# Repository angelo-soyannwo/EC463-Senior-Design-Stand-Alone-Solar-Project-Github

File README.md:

# Sol: An Alternative Off-grid Solar Configuration

## Quick-Start Info

### Structural Hardware

The hardware of our system consists of a frame with solar panels on either side, and a pair of reflectors in between. These reflectors slide diagonally up and down, and sideways along the rails of the frame, moved a stepper motor on either side and ball screws as the linear actuator. 3D printed components are used for interface between different parts, such as the stepper motor mount, sliding face plates, and ball screw rod attachers. Housing has also been developed for our PCBs, battery, and solar charge controller.

### Electronic Hardware

Most of our electronic pieces fit on a PCB. The light sensors and limit switches fit on the solar panels and rails of the frame respectively. The components on the PCB are: 2 Rpi Pico W's, a motor driver, buttons for Pico reset and manual motor control, 2 current sensors, and a temperature sensor. A Renogy solar charge controller is used externally to charge our battery with the solar panel, as well as power our system along with any other load.

### Control Pico Software

Our control software controls the movement of our reflectors through the stepper motors. The two stepper motors are connected in parallel to just one motor driver, so the code is made simple. Upon startup, the program moves the reflectors to their bottom-most position, where it will hit the bottom limit switch and begins tracking its position through step count. As of now, the position tracking is not an integral part of the system, since the program allows the reflectors to move upwards or downwards until they hit the limit switches; the position can be used for other purposes in the future. After startup and every ten seconds, the reflectors will check the light sensor readings, move a certain number of steps in a direction determined from the previous iteration, and check the light reading again. Based on the difference between the two readings, it will continue to move in the direction with more light or stop moving when the difference no longer passes a certain threshold. All of these parameters can be set in the software, including time between iterations and light difference threshold. Additionally, data from the light sensors are sent to our database on each iteration.

### Monitoring Pico Software

The monitoring software keeps track of charge and discharge current and voltage, and temperature of our system within the housing. It does so using two current/voltage sensor and one temperature sensor. The program first connects to WiFi, then begins the normal operation during which it sends data to our database every few seconds.

### Web Application

The web application uses a MERN stack (MongoDB, Express.js, React, Node.js). The web app takes data from our database on MongoDB, which in turn has data uploaded from our Pico servers. The user interface of the web app allows users to create an account, create arrays of our solar modules, and monitor solar panel output power, solar irradiation, and temperature across time. If any anomaly is detected, the user will receive an email such that they can check up on the system as soon as they can.

Link to Web Application: https://sol-ec-464-team-15.netlify.app/

Solar Array Id: 65539e775435e37264e3e6ff

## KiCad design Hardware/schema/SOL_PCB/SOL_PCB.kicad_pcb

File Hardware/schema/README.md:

# Brief PCB Netlist Explanation

Netlist Explanations :
 - Load + = Load from solar charge controller
 - Load - = Return path from solar charge controller. This is ground.
 - Vin P + = Positive from solar panels
 - Vin P - = Negative from solar panels
 - 3.3V_M = 3.3V from monitoring pico
 - 3.3V_C = 3.3V from control pico
 - 5V = Input from a 12V-5V converter. This is an external component
 - VCC = Vin -  from the INA219. This is 12V, and is idential to Load+.

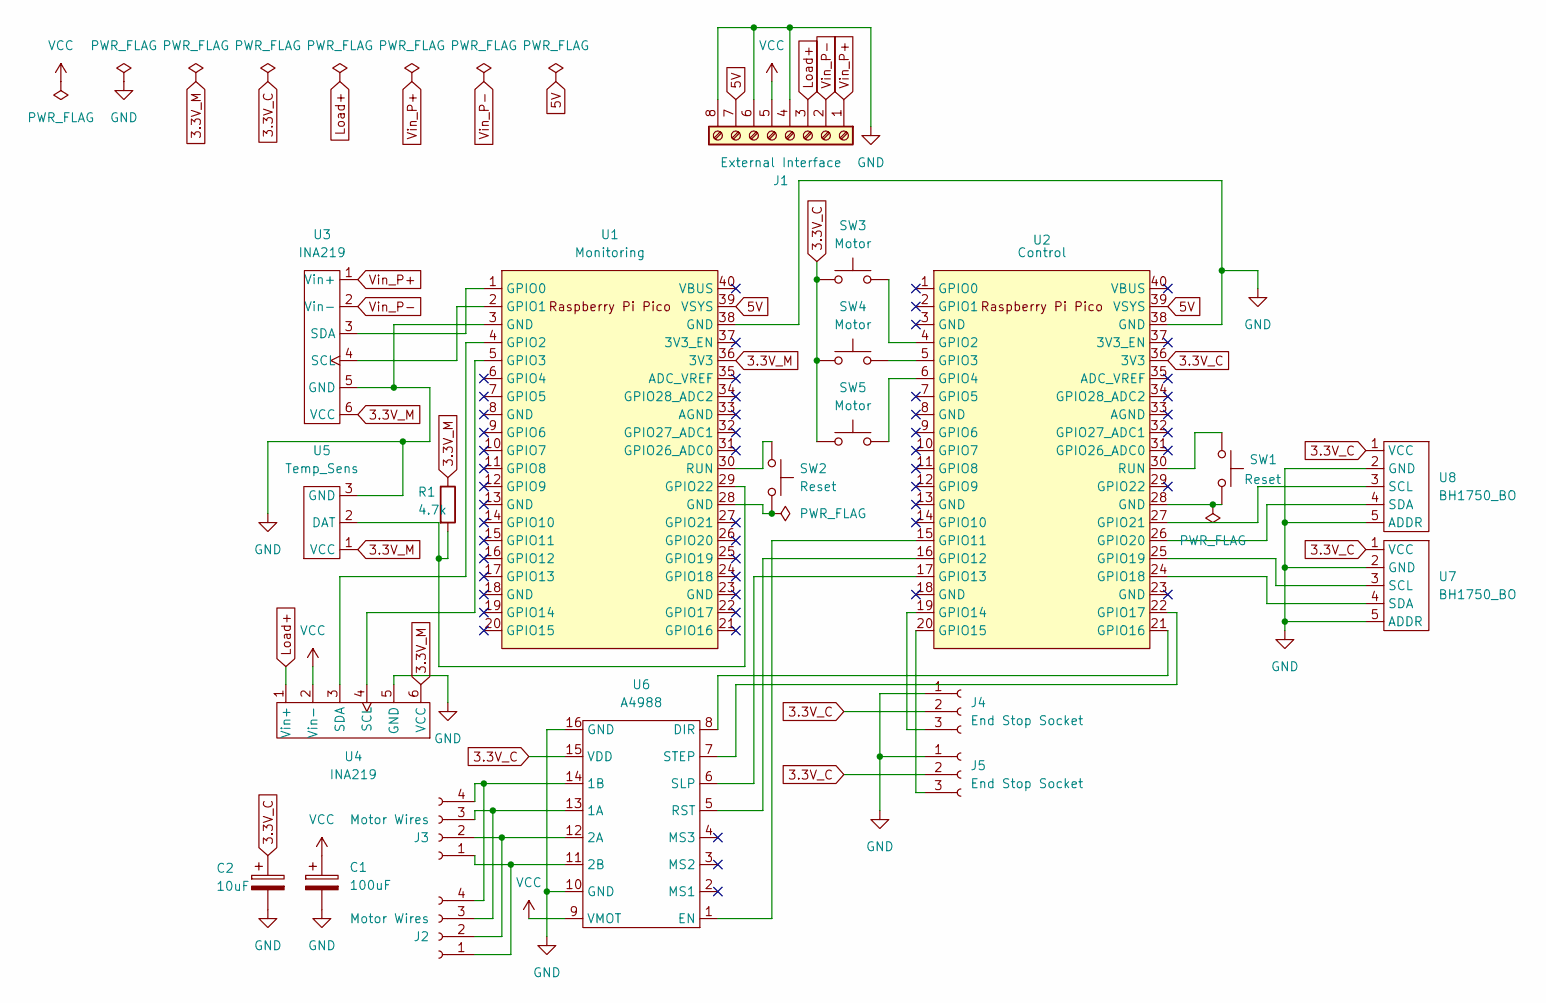
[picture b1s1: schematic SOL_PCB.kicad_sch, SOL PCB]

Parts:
C1: 100uF; CP_Radial_D6.3mm_P2.50mm
C2: 10uF; CP_Radial_D5.0mm_P2.50mm
J1: External Interface; TerminalBlock_Phoenix_MKDS-1,5-8_1x08_P5.00mm_Horizontal
J2, J3: Motor Wires; PinSocket_1x04_P2.54mm_Vertical
J4, J5: End Stop Socket; PinSocket_1x03_P2.54mm_Vertical
R1: 4.7k; R_Axial_DIN0207_L6.3mm_D2.5mm_P15.24mm_Horizontal
SW1, SW2: Reset; SW_PUSH_6mm_H4.3mm
SW3, SW4, SW5: Motor; SW_PUSH_6mm_H4.3mm
U1: Monitoring; RPi_Pico_SMD_TH
U2: Control; RPi_Pico_SMD_TH
U3, U4: INA219; INA219_Breakout
U5: Temp_Sens; Temp_Sensor
U6: A4988; A4988 Driver
U7, U8: BH1750_BO; BH1750

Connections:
3.3V_C: C2.1, J4.2, J5.2, SW3.1, SW4.1, SW5.1, U2.36 (3V3), U6.15 (VDD), U7.1 (VCC), U8.1 (VCC)
3.3V_M: R1.1, U1.36 (3V3), U3.6 (VCC), U4.6 (VCC), U5.1 (VCC)
5V: J1.7, U1.39 (VSYS), U2.39 (VSYS)
GND: C1.2, C2.2, J1.4, J1.6, J1.8, J4.1, J5.1, U1.3 (GND), U1.38 (GND), U2.38 (GND), U3.5 (GND), U4.5 (GND), U5.3 (GND), U6.10 (GND), U6.16 (GND), U7.2 (GND), U7.5 (ADDR), U8.2 (GND), U8.5 (ADDR)
Load+: J1.3, U4.1 (Vin+)
unnamed: J2.1, J3.1, U6.11 (2B)
unnamed: J2.2, J3.2, U6.12 (2A)
unnamed: J2.3, J3.3, U6.13 (1A)
unnamed: J2.4, J3.4, U6.14 (1B)
unnamed: J4.3, U2.19 (GPIO14)
unnamed: J5.3, U2.20 (GPIO15)
unnamed: SW1.2, U2.28 (GND)
unnamed: SW2.2, U1.28 (GND)
unnamed: U1.1 (GPIO0), U3.3 (SDA)
unnamed: U1.2 (GPIO1), U3.4 (SCL)
unnamed: U1.4 (GPIO2), U4.3 (SDA)
unnamed: U1.5 (GPIO3), U4.4 (SCL)
unnamed: R1.2, U1.29 (GPIO22), U5.2 (DAT)
unnamed: SW2.1, U1.30 (RUN)
unnamed: SW3.2, U2.4 (GPIO2)
unnamed: SW4.2, U2.5 (GPIO3)
unnamed: SW5.2, U2.6 (GPIO4)
unnamed: U2.15 (GPIO11), U6.1 (EN)
unnamed: U2.16 (GPIO12), U6.5 (RST)
unnamed: U2.17 (GPIO13), U6.6 (SLP)
unnamed: U2.21 (GPIO16), U6.8 (DIR)
unnamed: U2.22 (GPIO17), U6.7 (STEP)
unnamed: U2.24 (GPIO18), U7.4 (SDA)
unnamed: U2.25 (GPIO19), U7.3 (SCL)
unnamed: U2.26 (GPIO20), U8.4 (SDA)
unnamed: U2.27 (GPIO21), U8.3 (SCL)
unnamed: SW1.1, U2.30 (RUN)
VCC: C1.1, J1.5, U4.2 (Vin-), U6.9 (VMOT)
Vin_P+: J1.1, U3.1 (Vin+)
Vin_P-: J1.2, U3.2 (Vin-)

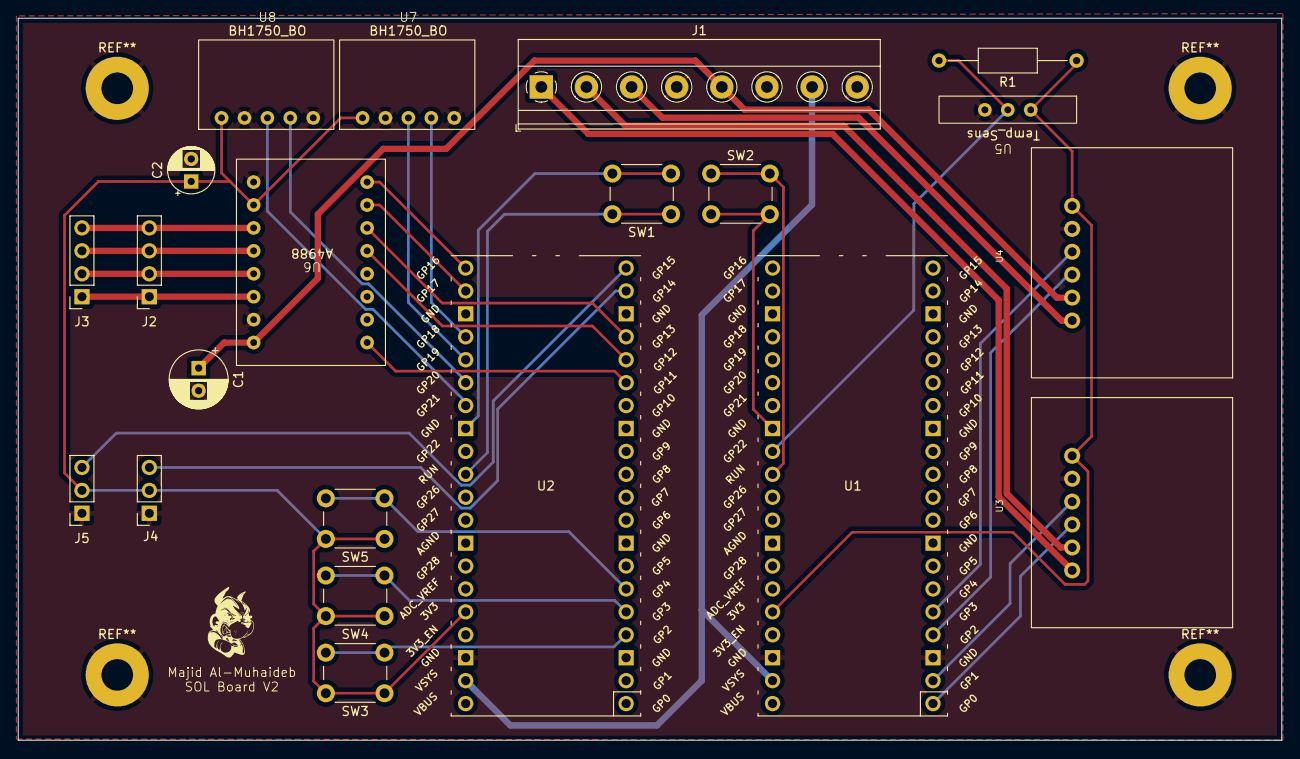
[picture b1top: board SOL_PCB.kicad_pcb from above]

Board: 2 copper layers, 140.0 x 80.0 mm, 21 parts (0 on the bottom side), 35 nets.

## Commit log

2023-10-27 Project initialized
2023-10-30 Working front page routing needs to be done (hard)
2023-10-30 Fixed Routing (still need to do page links)
2023-10-30 Fixed Routing (need to start login and sign up)
2023-10-30 updated so root is no longer included
2023-11-02 Bu guest wifi test programs updated
2023-11-03 I fixed the sign-up feature
2023-11-03 Login is working
2023-11-10 working get requests and login functionality
2023-11-11 Moved Database to Cloud provider Service
2023-11-11 wrote some documentation for how to run the app
2023-11-11 wrote some more documentation
2023-11-11 removed application server (it didn't do anything anyway)
2023-11-11 formatted README.md
2023-11-11 Pico w was able to make post request to cloud atlas database
2023-11-14 ready for tests
2023-11-14 Updated formatting
2024-01-30 plotting dummy data works
2024-02-01 updated Analytics page
2024-02-28 Finished up to second test
2024-03-05 Multiple graphs now render to the web page
2024-03-15 RTC_wifi and overall structure of motor control
2024-03-15 Pre-physical testing, works as expected on laptop
2024-03-16 Fixed network connection issue, add LED indications
2024-03-23 Manual control with LCD
2024-03-24 Combine auto and manual control with asyncio (cooperative multitasking)
2024-03-27 added pico files
2024-04-04 Delete pico_web_server/bh1750.py(BH1750 library).py
    All the libraries are in the updated_monitoring_system folder
2024-04-04 updated code to add anomalous data to database
2024-04-09 updated website and have completed email code
2024-04-10 Auto rotate based on light maximizing. Interrupts in limSwitch, asynchronous cooperative multitasking between manualMotor and lightTrackerMain, motor disabled when not in use. In testing.
2024-04-10 removed queue, replace with global variable currSteps in limSwitch. Will replace cooperative multitasking with interrupts for activating manualMotor
2024-04-11 Replaced cooperative multitasking for manual mode with an interrupt. Not yet tested.
2024-04-11 Organization
2024-04-11 Fixed bugs with new infrastructure. Need to incorporate light sensor data sending next.
2024-04-16 Combined motor control and light data-sending code
2024-04-17 Fixed issues from physical testing, 4/16
2024-04-19 Changes from final retest 4/18
2024-04-20 Removed duplicate function definitions in temperature_current_main.py, main.py is the same as temperature_current_main.py
2024-04-25 Reorganized folders (added upload folders with only files needed for the Picos
2024-04-25 Moved old code to working files folder
2024-04-27 Added hardware folder
2024-04-27 Added readme & files
2024-04-27 Added PCB notes
2024-04-27 Dash spaces
2024-04-27 Added printing settings
2024-04-27 Moved pico web server folder to working files folder
2024-04-27 Added READMEs, changed name of Sol to Web_App, added previous reports
2024-04-27 Created software folder with control, monitoring, and web app. Added Software report (README_SOFTWARE.md). Renamed hardware report to README_HARWARE.md.
2024-04-27 Fixed flow diagram issues
2024-04-27 Rename README_HARDWARE.md to README.md
2024-04-27 Rename README_SOFTWARE.md to README.md
2024-05-02 Sol website done
2024-05-02 Ready to deploy
2024-05-03 ready to deploy on netlify
2024-05-03 removed package-lock.json
2024-05-03 changed port bindings
2024-05-04 updated Read me's
2024-05-12 added solar array ID
